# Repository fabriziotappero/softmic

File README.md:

# Software-Defined Microphone

This is the home of *Software-Defined Microphone*, a quite special
high-quality wireless microphone designed to allow you to focus on the artistic
aspect of sound recording.

The basic idea is a microphone that includes all the necessary on-board 
software so that compression, noise reduction, volume control is magically done
by the microphone itself. The ultimate goal of this microphone is to let the
microphone take care of the technicalities so that you can concentrate on the 
artistic aspect of sound recording.

In this picture you can see a the first prototype of *Software-Defined Microphone*.

*Software-Defined Microphone* is completely  open source: schematics, circuit 
simulations, mechanical drawings and software code.

## Repository Folder Structure
This is the folder structure of this project.
```
root
│   README.md               The file your are reading
│   license.md              License file    
└───sch                     Schematics and PCB fab files done in KiCad
│   │   softmic.pro
│   │   softmic.sch
│   │   softmic.kicad_pcb
│   └───lib                 Kicad library files
│   └───pdf                 IC data sheets
└───sim                     Simulated circuits in LT Spice
│   │   softmic-sim.asc
│   └───lib                 LT Spice library  
└───src                     Micropython ESP32 code
└───mec                     Mechanical parts designed in Blender
└───img                     Various images
└───tmp                     generic data sheets and additional info
```
## Starting point
I actually own a [Samson C02](https://www.amazon.com/s?k=samsons+c02) condenser
microphone that I use together with a [Tascam DR-40](https://www.amazon.com/s?k=tascam+dr-40).
[Here](https://soundcloud.com/cinema_sound/samson-c02-dx-pop-filter) 
an example of what the Samson C02 sounds like 
and following, the picture of the inside of my Samson C02.

Here you can see the actual schematic of the Samson C02 (courtesy of *the Internet*). 
Nothing really mind-blowing but functional.

For the time being this is the starting point of this project. The objective of 
this project is to make something of a similar quality but *software-oriented*.

## Microphone Capsule
This microphone is designed to function with an **electret capsule** similar to the
[Primo EM173](sch/pdf/PrimoEM173.pdf), an
electret capsule with an internal FET. For some additional flexibility the use of
a simpler electret capsule without FET (e.g. the 
[Transsound TSB160A](img/TSB160A.jpg) from the 
Samson C02) will be possible too.

## Microphone System Design
Let us see a detailed list of features of this microphone. Some of these features
are still unimplemented.

1. The microphone uses a standard **electret microphone capsule** with a standard 
 internal FET. The use of a electret microphone without FET is possible too.

2. a traditional 3.5mm stereo headphone jack output (unbalanced line out) allows 
the microphone to be connected to a pair of standard headphones for monitoring 
purposes.

3. A standard XLR connector offers a balanced audio output. This allows this
microphone to be interfaced with any traditional audio equipment.

4. When provided externally via the XLR connector, phantom power can power the 
microphone. (UNIMPLEMENTED)

5. A Bluetooth/WiFi output allows to connect without cables to a camera, 
smartphone or PC.

6. When using Bluetooth/WiFi, multiple microphones can be all connected among
them. (UNIMPLEMENTED)

7. An internal 1-cell lithium battery can power the microphone for approximately
10h. This battery is rechargeable via a USB-C connector.

4. When provided externally via the XLR connector, phantom power can recharge the 
internal lithium battery. (UNIMPLEMENTED)

8. The microphone is equipped with a fairly powerful dual-core
processor re-programmable over the WiFi connection or over USB-C. The processor
programming is done in [Micropython](https://micropython.org/).

9. To ease connectivity with other accessories the microphone is equipped
with one-does-it-all small multi-pin connector. (UNIMPLEMENTED)

10. A spring connector similar to the 
[Coda Systems PCB sprint connector](img/codaSystemsSpringConn.jpg) allows the 
microphone to be connected to or power other accessories. (UNIMPLEMENTED)

11. A small LCD outputs all necessary microphone information.

12. Few push buttons allow to interact with the microphone.

13. The internal ESP32 dual-core processor allows the realtime processing of the
audio signal coming in. (UNIMPLEMENTED)

## Circuit Schematics
In the following figure you can see the KiCad schematic of softmic done in KiCad.

## Mechanical Parts
A full fledged microphone is not only made of its electronics, mechanical parts 
are equally important.

Any mechanical parts in this projects are made with non-destructive modeling 
using [Blender](https://www.blender.org) version 2.8. 
For a quick start have a look at this 
[great tutorial](https://www.youtube.com/watch?v=WzwmkYhlrcQ).

## License
Copyright (c) 2020 Fabrizio Tappero

Permission is hereby granted, free of charge, to any person obtaining a copy of 
this software and associated documentation files (the "Software"), to deal in 
the Software without restriction, including without limitation the rights to 
use, copy, modify, merge, publish, distribute, sublicense, and/or sell copies 
of the Software, and to permit persons to whom the Software is furnished to do 
so, subject to the following conditions:

The above copyright notice and this permission notice shall be included in all 
copies or substantial portions of the Software.

THE SOFTWARE IS PROVIDED "AS IS", WITHOUT WARRANTY OF ANY KIND, EXPRESS OR 
IMPLIED, INCLUDING BUT NOT LIMITED TO THE WARRANTIES OF MERCHANTABILITY, 
FITNESS FOR A PARTICULAR PURPOSE AND NONINFRINGEMENT. IN NO EVENT SHALL THE 
AUTHORS OR COPYRIGHT HOLDERS BE LIABLE FOR ANY CLAIM, DAMAGES OR OTHER 
LIABILITY, WHETHER IN AN ACTION OF CONTRACT, TORT OR OTHERWISE, ARISING 
FROM, OUT OF OR IN CONNECTION WITH THE SOFTWARE OR THE USE OR OTHER 
DEALINGS IN THE SOFTWARE.

## References
A lot of microphone and microphone-related products and devices exists out there.
Here is what it can be considered a good starting point.

[Electret microphone](ttps://sound-au.com/articles/mic-electret.htm) and their
[electret Capsule](http://www.firstpr.com.au/rwi/mics/2009-09-a/).

[Microphone capsule Manufacturer](https://www.jlielectronics.com/microphone-capsules/?sort=pricedesc)
and one more [ capsule Manufacturer](https://microphone-parts.com/collections/capsules).

[Extensive RODE guy lecturer](https://www.youtube.com/watch?v=yKOH0DyRWRU&list=PLHoGZ7nuFTo8VmQBhzZxl-qDEIN7T5Vt8).
and some [audio Microphone Kits](https://microphone-parts.com/collections/mod-kits).

[Electret Amplifier Circuits](http://xtremecircuits.blogspot.com/2012/09/compressor-for-electret-microphone.html).

Some Texas instruments IC, [here](https://www.ti.com/lit/an/sboa320a/sboa320a.pdf) and 
[here](http://www.ti.com/lit/ug/tidu765/tidu765.pdf).

if you google *TS971 based Electret Condenser Microphone Amplifier* you get:
[this](https://robbietrumpet.com/soundcatchers.net/studio_recording_sound.htm), 
[this](https://www.instructables.com/id/Modify-a-cheap-LDC-Condenser-microphone/), 
[this](http://www.sdiy.org/oid/mics/Schoeps.gif) and 
[this](http://www.zen22142.zen.co.uk/Circuits/Audio/ecmmic.htm).

[Some electret capsules](https://www.abcomponents.co.uk/product-category/electret-microphones/) and 
[this](https://micbooster.com/12-primo-microphone-capsules) and 
[this](https://micbooster.com/content/12-comparison-table-for-primo-microphone-capsules).

Very interesting [electret capsules](https://micbooster.com/primo-microphone-capsules/9-em173.html)
and [some more](https://micbooster.com/primo-microphone-capsules/8-primo-em172.html) plus the 
[very best electret capsule](http://www.micbooster.com/documents/EM173%20Oct%202011.pdf).

[Application Note about LSK489](http://www.linearsystems.com/lsdata/others/LSK489_Application_Note.pdf).

[Interesting capacity multiplier](http://www.audioimprov.com/AudioImprov/Mics/Entries/2014/12/18_Another_Chinese_mic_Circuit.html).

[Samson C02 internal circuit](http://www.audioimprov.com/AudioImprov/Mics/Entries/2015/4/23_Basic_FET_Microphone_Circuits.html).

[Popular Alice schematic](http://scotthelmke.com/alice-mic.html).

[How to bias a JFET](http://www.vishay.com/docs/70595/70595.pdf).

[Audio compressor](https://www.electroschematics.com/audio-compressor-agc/).

[Audio Op Amp IC from Texas Instrument](http://www.ti.com/lit/ds/symlink/opa1678.pdf).

Interesting [blog post](https://www.diyaudio.com/forums/equipment-and-tools/319784-search-ultra-quality-electret-mic-interface-circuit.html) and 
[here](https://www.electronics-lab.com/project/low-noise-mini-electret-microphone-preamplifier/),
[here](http://www.johncon.com/john/wm61a/) 
and [here](http://www.micbooster.com/documents/EM173%20Oct%202011.pdf).

[Interesting audio people](https://micbooster.com/)

[Interesting microphone case](https://eu.mouser.com/Wire-Cable/Wire-Cable-Management/Cable-Glands-Strain-Reliefs-Cord-Grips/_/N-fb8zo) and [one more](https://eu.mouser.com/datasheet/2/18/inhouse_Amphenol_C146%20Series_Accessories_VN16-1158081.pdf).

[Audio Preamp product](https://www.bhphotovideo.com/c/product/292989-REG/Sound_Devices_MM_1_MM_1_Single_Channel_Portable.html/overview) and one more 
[reference audio preamp](http://www.hiroshi.com.hk/en/product/detail/mini-microphone-pre-amplifier-23#.Xn4073Io_ws)
that I actually own.

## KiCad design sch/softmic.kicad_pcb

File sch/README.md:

Schematic files for the creation of the PCB done using the open-source software KICAD available from:

https://www.kicad-pcb.org/

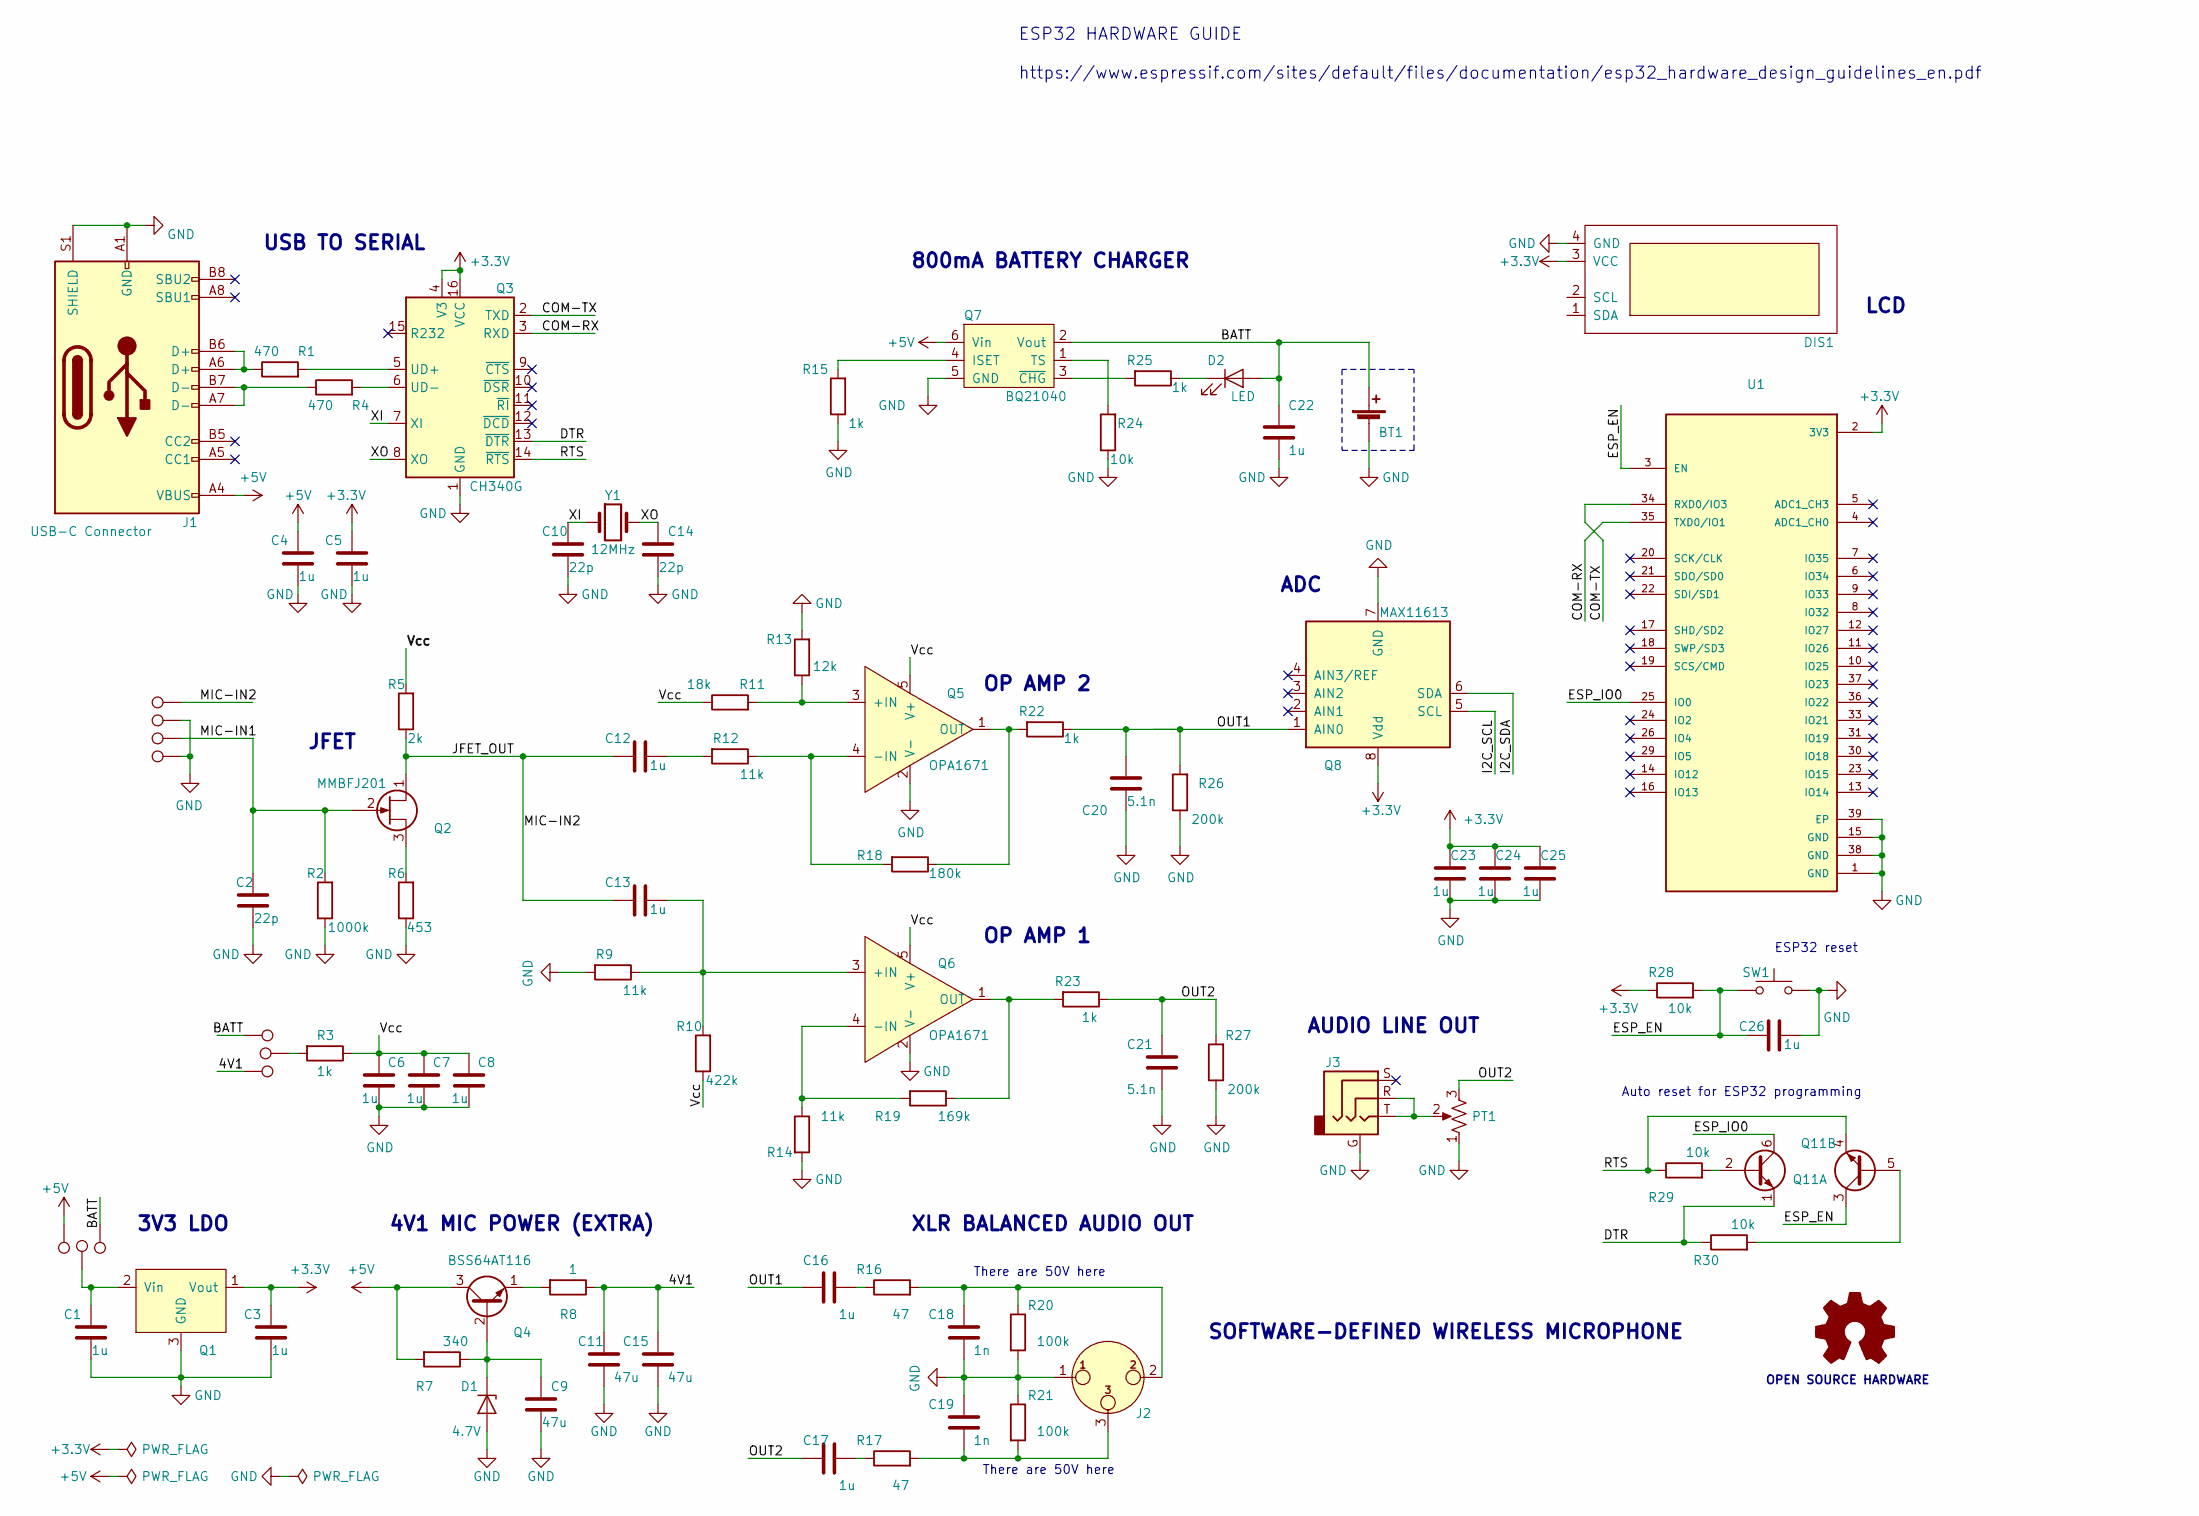
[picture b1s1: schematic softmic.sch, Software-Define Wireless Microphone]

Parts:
BT1: 1-Cell Litium Battery; BatteryHolder18650; Mouser PN none; Digikey PN none
C1, C3, C4, C5, C6, C7, C8, C12, C13, C16, C17, C22, C23, C24, C25, C26: 1u; C_0805_2012Metric_Pad1.15x1.40mm_HandSolder; MPN HMK212BC7105MGHT; Digikey PN none
C2, C10, C14: 22p; C_0805_2012Metric_Pad1.15x1.40mm_HandSolder; MPN none; Digikey PN none
C9, C11, C15: 47u; C_0805_2012Metric_Pad1.15x1.40mm_HandSolder; MPN LMK316BC6476ML-T; Digikey PN none
C18, C19: 1n; C_0805_2012Metric_Pad1.15x1.40mm_HandSolder; MPN none; Digikey PN none
C20, C21: 5.1n; C_0805_2012Metric_Pad1.15x1.40mm_HandSolder; MPN none; Digikey PN none
D1: 4.7V; D_SOD-123; MPN BZT52C4V7-E3-08; Digikey PN 112-BZT52C4V7-E3-08CT-ND
D2: LED; LED_0805_2012Metric_Pad1.15x1.40mm_HandSolder; Mouser PN 710-150080RS75000; Digikey PN 732-4984-1-ND
DIS1: Oled_128_32; OLED-0.91-128x32; MPN none; Digikey PN none
J1: USB-C Connector; USB_C_Receptacle_GCT_USB4085; MPN USB4085-GF-A; Digikey PN 2073-USB4085-GF-ACT-ND
J2: XLR-OUT; XLR-NC3MAAH-1; MPN NC3MAAH-1; Digikey PN none
J3: AudioJack 3.5mm; SJ-43514-SM; MPN SJ-43514-SMT-TR; Digikey PN CP-43514SJCT-ND
P1, P2, P3, P8, P9: 4V1; TestPoint_THTPad_D1.5mm_Drill0.7mm; MPN none; Digikey PN none
P4, P5, P6, P7: none; TestPoint_THTPad_D1.5mm_Drill0.7mm; MPN none; Digikey PN none
P10: VccPad; TestPoint_THTPad_D1.5mm_Drill0.7mm; MPN none; Digikey PN none
PT1: 200k; Potentiometer_Bourns_3224W_Vertical; MPN PVG3G204C01R00; Digikey PN PVG3G204C01R00
Q1: MCP1812BT-033; SOT-23; MPN MCP1812BT-033/TT; Digikey PN MCP1812BT-033/TTTR-ND
Q2: MMBFJ201; SOT-23; MPN MMBFJ201; Digikey PN MMBFJ201CT-ND
Q3: CH340G; SOIC-16_3.9x9.9mm_P1.27mm; MPN CH340G; LCSC PN C14267
Q4: BSS64AT116; SOT-23; MPN BSS64AT116; Digikey PN BSS64AT116CT-ND
Q5, Q6: OPA1671; SOT-23-5; MPN OPA1671IDBVR; Digikey PN 296-OPA1671IDBVRCT-ND
Q7: BQ21040; SOT-23-6; MPN BQ21040DBVT; Digikey PN 296-44196-1-ND
Q8: MAX11613; MSOP-8_3x3mm_P0.65mm; MPN MAX11613EUA+T; Digikey PN MAX11613EUA+CT-ND
Q11: BC847BS-TP; SOT-363_SC-70-6; Mouser PN 833-BC847BS-TP
R1, R4: 470; R_0805_2012Metric_Pad1.15x1.40mm_HandSolder; MPN none; Digikey PN none
R2: 1000k; R_0805_2012Metric_Pad1.15x1.40mm_HandSolder; MPN none; Digikey PN none
R3, R15, R22, R23, R25: 1k; R_0805_2012Metric_Pad1.15x1.40mm_HandSolder; MPN none; Digikey PN none
R5: 2k; R_0805_2012Metric_Pad1.15x1.40mm_HandSolder; MPN none; Digikey PN none
R6: 453; R_0805_2012Metric_Pad1.15x1.40mm_HandSolder; MPN none; Digikey PN none
R7: 340; R_0805_2012Metric_Pad1.15x1.40mm_HandSolder; MPN none; Digikey PN none
R8: 1; R_0805_2012Metric_Pad1.15x1.40mm_HandSolder; MPN none; Digikey PN none
R9, R12, R14: 11k; R_0805_2012Metric_Pad1.15x1.40mm_HandSolder; MPN none; Digikey PN none
R10: 422k; R_0805_2012Metric_Pad1.15x1.40mm_HandSolder; MPN none; Digikey PN none
R11: 18k; R_0805_2012Metric_Pad1.15x1.40mm_HandSolder; MPN none; Digikey PN none
R13: 12k; R_0805_2012Metric_Pad1.15x1.40mm_HandSolder; MPN none; Digikey PN none
R16, R17: 47; R_0805_2012Metric_Pad1.15x1.40mm_HandSolder; MPN none; Digikey PN none
R18: 180k; R_0805_2012Metric_Pad1.15x1.40mm_HandSolder; MPN none; Digikey PN none
R19: 169k; R_0805_2012Metric_Pad1.15x1.40mm_HandSolder; MPN none; Digikey PN none
R20, R21: 100k; R_0805_2012Metric_Pad1.15x1.40mm_HandSolder; MPN none; Digikey PN none
R24, R28, R29, R30: 10k; R_0805_2012Metric_Pad1.15x1.40mm_HandSolder; MPN none; Digikey PN none
R26, R27: 200k; R_0805_2012Metric_Pad1.15x1.40mm_HandSolder; MPN none; Digikey PN none
SW1: RST; SW_SPST_FSMSM; MPN PTS636SM43SMTRLF; Digikey PN none
U1: ESP32-WROVER-B 16MB; ESP32-WROVER-B_(16MB); MPN ESP32-WROVER-B (16MB); LCSC PN none
Y1: 12MHz; Crystal_SMD_5032-2Pin_5.0x3.2mm; MPN TCX Corporation; LCSC PN none
logo1: Logo_Open_Hardware_Small; OSHW-Logo2_9.8x8mm_SilkScreen

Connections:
+3V3: C3.2, C5.2, C23.2, C24.2, C25.2, DIS1.3 (VCC), Q1.1 (Vout), Q3.4 (V3), Q3.16 (VCC), Q8.8 (Vdd), R28.1, U1.2 (3V3)
+5V: C4.2, J1.A4 (VBUS), J1.A9 (VBUS), J1.B4 (VBUS), J1.B9 (VBUS), P1.1, Q4.3 (C), Q7.6 (Vin), R7.2
/4V1: C11.1, C15.1, P9.1, R8.1
/BATT: BT1.1 (+), C22.2, D2.2 (A), P3.1, P8.1, Q7.2 (Vout)
/COM-RX: Q3.3 (RXD), U1.35 (TXD0/IO1)
/COM-TX: Q3.2 (TXD), U1.34 (RXD0/IO3)
/DTR: Q3.13 (~DTR), Q11.1 (E1), R30.1
/ESP_EN: C26.2, Q11.3 (C2), R28.2, SW1.1, U1.3 (EN)
/ESP_IO0: Q11.6 (C1), U1.25 (IO0)
/I2C_SCL: Q8.5 (SCL)
/I2C_SDA: Q8.6 (SDA)
/JFET_OUT: C12.2, C13.2, P4.1, Q2.1 (D), R5.1
/MIC-IN1: C2.1, P6.1, Q2.2 (G), R2.2
/OUT1: C16.2, C20.1, Q8.1 (AIN0), R22.1, R26.2
/OUT2: C17.2, C21.1, PT1.3, R23.1, R27.2
/RTS: Q3.14 (~RTS), Q11.4 (E2), R29.1
/Vcc: C6.2, C7.2, C8.2, Q5.5 (V+), Q6.5 (V+), R3.1, R5.2, R10.1, R11.1
/XI: C10.1, Q3.7 (XI), Y1.1
/XO: C14.1, Q3.8 (XO), Y1.2
GND: BT1.2 (-), C1.1, C2.2, C3.1, C4.1, C5.1, C6.1, C7.1, C8.1, C9.2, C10.2, C11.2, C14.2, C15.2, C18.1, C19.2, C20.2, C21.2, C22.1, C23.1, C24.1, C25.1, C26.1, D1.2 (A), DIS1.4 (GND), J1.A1 (GND), J1.A12 (GND), J1.B1 (GND), J1.B12 (GND), J1.S1 (SHIELD), J2.1, J3.G, P5.1, P7.1, PT1.1, Q1.3 (GND), Q3.1 (GND), Q5.2 (V-), Q6.2 (V-), Q7.5 (GND), Q8.7 (GND), R2.1, R6.1, R9.2, R13.2, R14.2, R15.1, R20.2, R21.1, R24.1, R26.1, R27.1, SW1.2, U1.1 (GND), U1.15 (GND), U1.38 (GND), U1.39 (EP)
unnamed: C1.2, P2.1, Q1.2 (Vin)
unnamed: C9.1, D1.1 (K), Q4.2 (B), R7.1
unnamed: C12.1, R12.2
unnamed: C13.1, Q6.3 (+IN), R9.1, R10.2
unnamed: C16.1, R16.1
unnamed: C17.1, R17.1
unnamed: C18.2, J2.2, R16.2, R20.1
unnamed: C19.1, J2.3, R17.2, R21.2
unnamed: D2.1 (K), R25.1
unnamed: J1.A6 (D+), J1.B6 (D+), R1.1
unnamed: J1.A7 (D-), J1.B7 (D-), R4.1
unnamed: J3.R, J3.T, PT1.2
unnamed: P10.1, R3.2
unnamed: Q2.3 (S), R6.2
unnamed: Q3.5 (UD+), R1.2
unnamed: Q3.6 (UD-), R4.2
unnamed: Q4.1 (E), R8.2
unnamed: Q5.1 (OUT), R18.1, R22.2
unnamed: Q5.3 (+IN), R11.2, R13.1
unnamed: Q5.4 (-IN), R12.1, R18.2
unnamed: Q6.1 (OUT), R19.1, R23.2
unnamed: Q6.4 (-IN), R14.1, R19.2
unnamed: Q7.1 (TS), R24.2
unnamed: Q7.3 (~CHG), R25.2
unnamed: Q7.4 (ISET), R15.2
unnamed: Q11.2 (B1), R29.2
unnamed: Q11.5 (B2), R30.2

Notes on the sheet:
OPEN SOURCE HARDWARE
3V3 LDO
XLR BALANCED AUDIO OUT
OP AMP 1
OP AMP 2
JFET
800mA BATTERY CHARGER
ADC
USB TO SERIAL
LCD
SOFTWARE-DEFINED WIRELESS MICROPHONE
4V1 MIC POWER (EXTRA)
AUDIO LINE OUT
ESP32 HARDWARE GUIDE https://www.espressif.com/sites/default/files/documentation/esp32_hardware_design_guidelines_en.pdf
Auto reset for ESP32 programming
ESP32 reset
There are 50V here

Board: 2 copper layers, 87 parts (0 on the bottom side), 45 nets, no tracks yet.

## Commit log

2020-04-15 added schematic
2020-04-17 added more README info
2020-04-18 added feature/requirement list in README file
2020-04-18 added PDF datasheet of 3.5mm jack audio connector and ldo substitute for 3V3 output from 1-cell lithium battery
2020-04-18 in schematic, now LDO input can be USB 5V or internal battery
2020-04-18 added line out audio jack in schematic and PCB
2020-04-20 changed USB to serial IC, changed some footprints, changed RST SW
2020-04-20 changed USB-C connector type
2020-04-21 changed USB-C footprint and battery holder
2020-04-21 added small headphone volume potentiomenter
2020-04-21 changed all resistors to 0805 case resistors
2020-04-21 change all caps to 0805 case caps
2020-04-21 changed LED to red 0805 led
2020-04-21 pcb components placed
2020-04-21 first proto picture created
2020-04-21 schematic pdf updated
2020-05-04 changed ESP32 module for the 16MB version

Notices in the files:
sch/softmic.sch:
Copyright Fabrizio Tappero
parts and their libraries:
Copyright 2016 Accelerated Designs. All rights reserved.
